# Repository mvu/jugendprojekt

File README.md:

# jugendprojekt
This project has been moved to [gitlab.com](https://gitlab.com/jugendraum-feg-simmern/).

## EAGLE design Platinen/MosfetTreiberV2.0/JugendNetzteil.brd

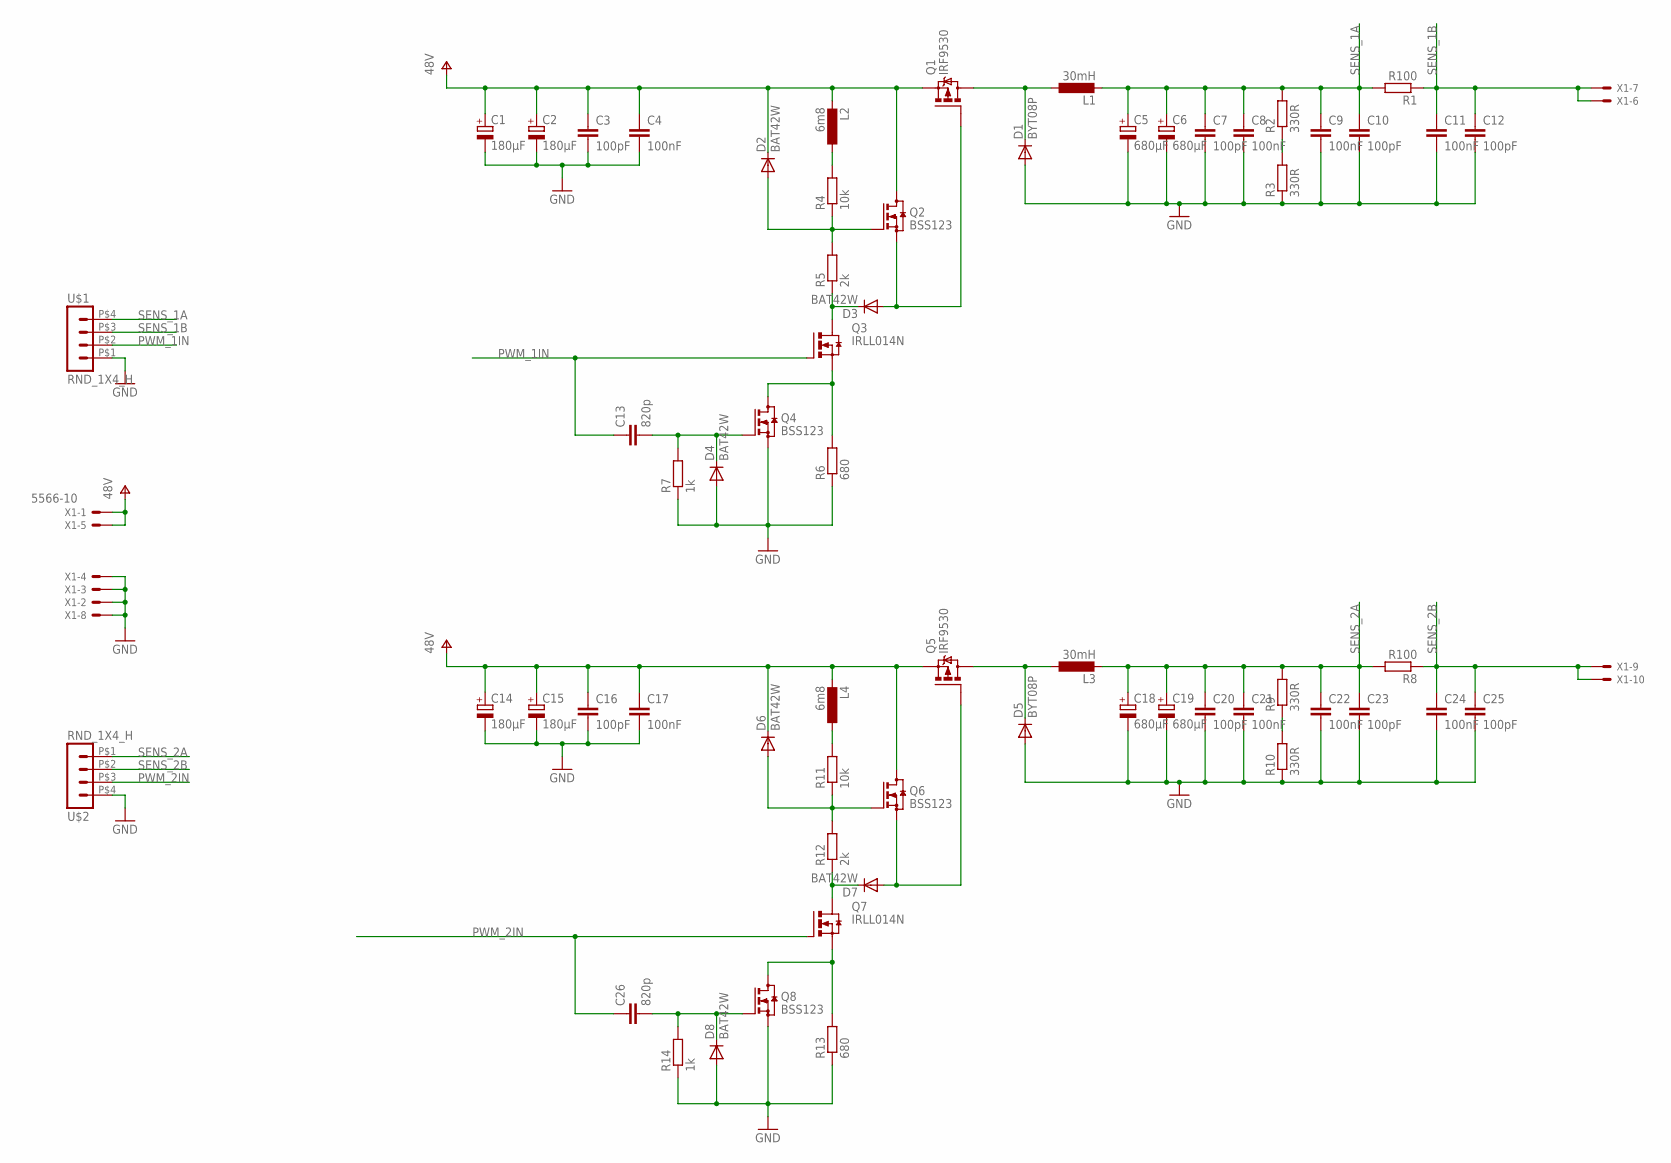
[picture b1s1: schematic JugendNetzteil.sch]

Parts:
C1, C2, C14, C15: 180µF; E3,5-8
C3, C7, C10, C12, C16, C20, C23, C25: 100pF; C0805
C4, C8, C9, C11, C17, C21, C22, C24: 100nF; C0805
C5, C6, C18, C19: 680µF; TT5D11
C13, C26: 820p; C0805
D1, D5: BYT08P; TO220ACS
D2, D3, D4, D6, D7, D8: BAT42W; SOD123
L1, L3: 30mH; TJ8-U1
L2, L4: 6m8; 2200-15.24
Q1, Q5: IRF9530; TO220BV
Q2, Q4, Q6, Q8: BSS123; SOT23
Q3, Q7: IRLL014N; SOT223
R1, R8: R100; 0617V
R2, R3, R9, R10: 330R; 0414V
R4, R11: 10k; R0805
R5, R12: 2k; R0805
R6, R13: 680; R0805
R7, R14: 1k; R0805
U$1, U$2: RND_1X4_H
X1: 5566-10

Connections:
GND: C1.-, C2.-, C3.2, C4.2, C5.-, C6.-, C7.2, C8.2, C9.2, C10.2, C11.2, C12.2, C14.-, C15.-, C16.2, C17.2, C18.-, C19.-, C20.2, C21.2, C22.2, C23.2, C24.2, C25.2, D1.A, D4.A, D5.A, D8.A, Q4.2 (S), Q8.2 (S), R3.1, R6.1, R7.1, R10.1, R13.1, R14.1, U$1.P$1 (1), U$2.P$4 (4), X1.2, X1.3, X1.4, X1.8
unnamed: C13.2, D4.C, Q4.1 (G), R7.2
unnamed: L2.1, R4.2
unnamed: D1.C, L1.1, Q1.D
unnamed: D3.A, Q1.G, Q2.2 (S)
unnamed: D3.C, Q3.2 (D), Q3.4 (D), R5.1
unnamed: D2.A, Q2.1 (G), R4.1, R5.2
unnamed: Q3.3 (S), Q4.3 (D), R6.2
unnamed: D6.A, Q6.1 (G), R11.1, R12.2
unnamed: L4.1, R11.2
unnamed: R2.1, R3.2
unnamed: D7.A, Q5.G, Q6.2 (S)
unnamed: D7.C, Q7.2 (D), Q7.4 (D), R12.1
unnamed: D5.C, L3.1, Q5.D
unnamed: C26.2, D8.C, Q8.1 (G), R14.2
unnamed: Q7.3 (S), Q8.3 (D), R13.2
unnamed: R9.1, R10.2
PWM_1IN: C13.1, Q3.1 (G), U$1.P$2 (2)
PWM_2IN: C26.1, Q7.1 (G), U$2.P$3 (3)
SENS_1A: C5.+, C6.+, C7.1, C8.1, C9.1, C10.1, L1.2, R1.2, R2.2, U$1.P$4 (4)
SENS_1B: C11.1, C12.1, R1.1, U$1.P$3 (3), X1.6, X1.7
SENS_2A: C18.+, C19.+, C20.1, C21.1, C22.1, C23.1, L3.2, R8.2, R9.2, U$2.P$1 (1)
SENS_2B: C24.1, C25.1, R8.1, U$2.P$2 (2), X1.9, X1.10
V+: C1.+, C2.+, C3.1, C4.1, C14.+, C15.+, C16.1, C17.1, D2.C, D6.C, L2.2, L4.2, Q1.S, Q2.3 (D), Q5.S, Q6.3 (D), X1.1, X1.5

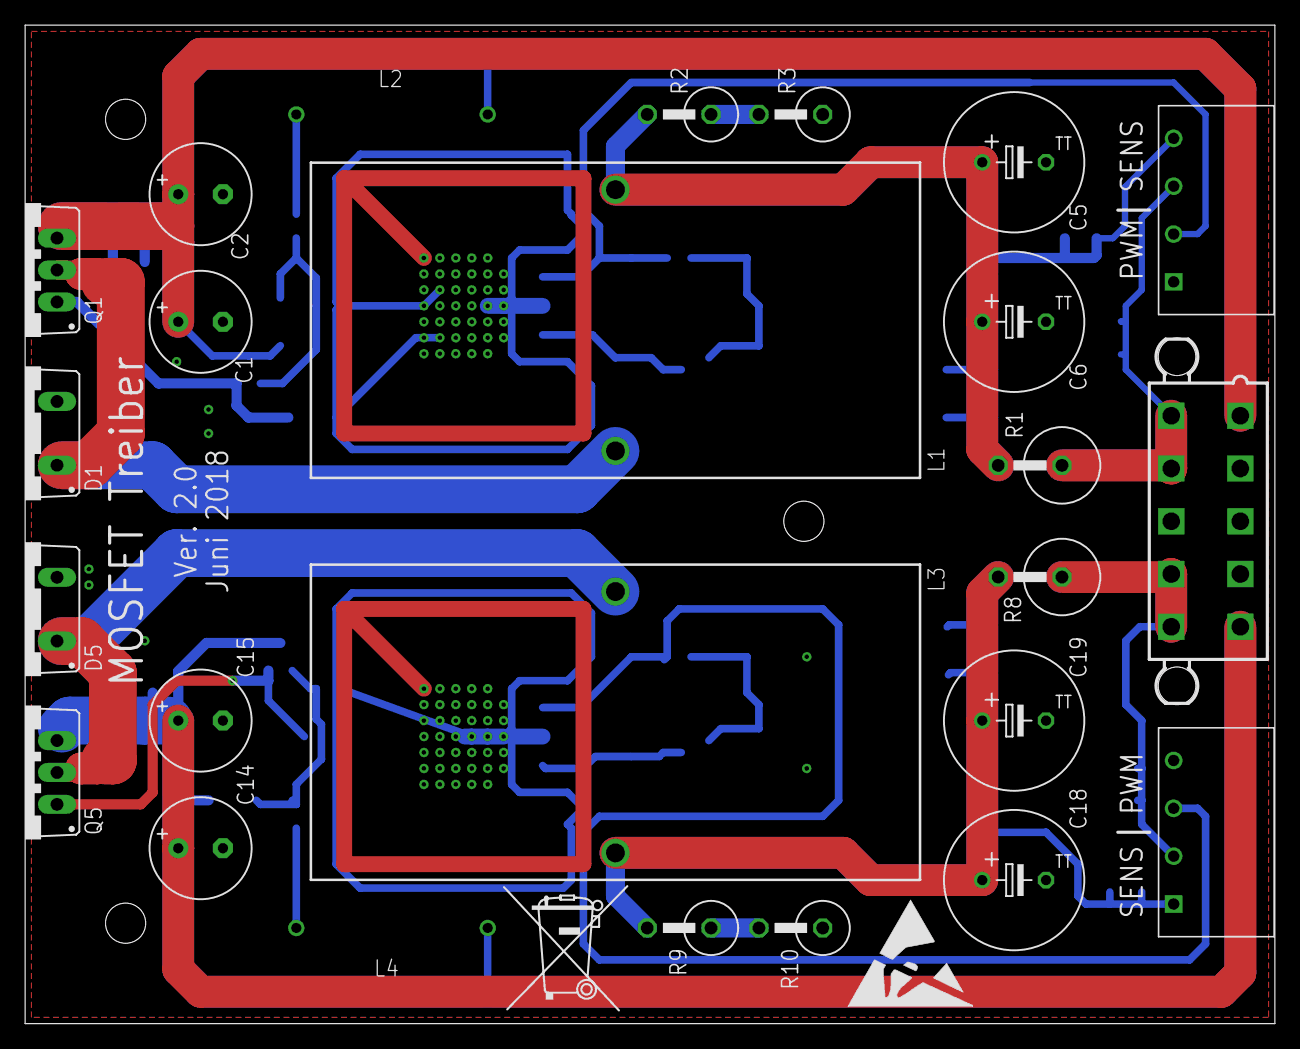
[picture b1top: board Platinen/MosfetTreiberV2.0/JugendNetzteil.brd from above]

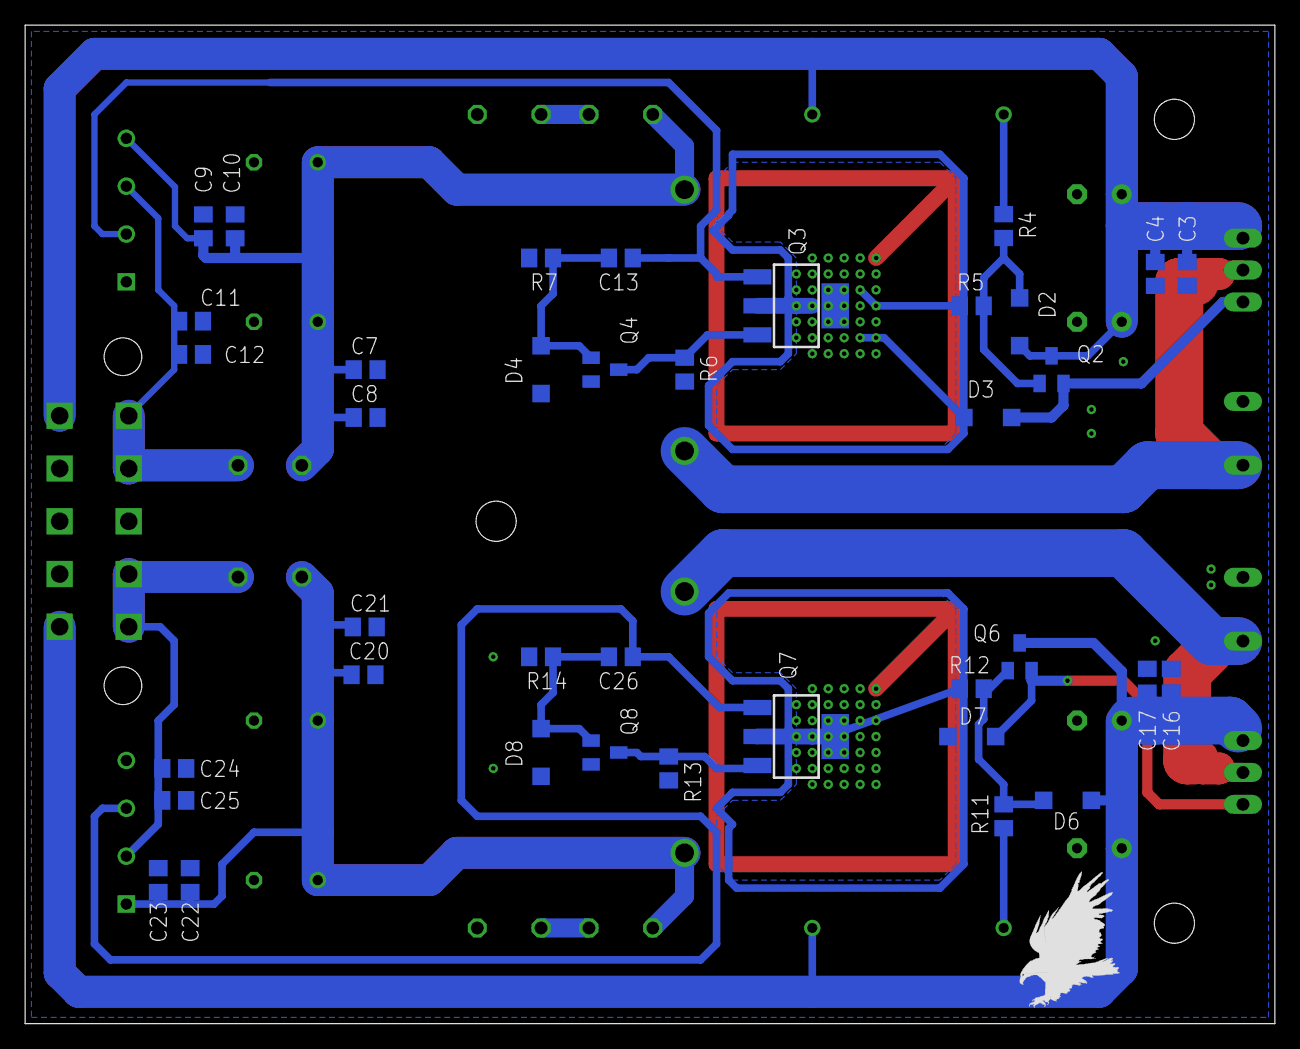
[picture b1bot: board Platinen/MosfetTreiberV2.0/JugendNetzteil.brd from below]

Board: 2 copper layers, 99.5 x 79.5 mm, 66 parts (39 on the bottom side), 24 nets.

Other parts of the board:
U$3: EAGLE-PLC-8MM
U$4: ESD_10.00
U$5: MUELLTONNE_10.00

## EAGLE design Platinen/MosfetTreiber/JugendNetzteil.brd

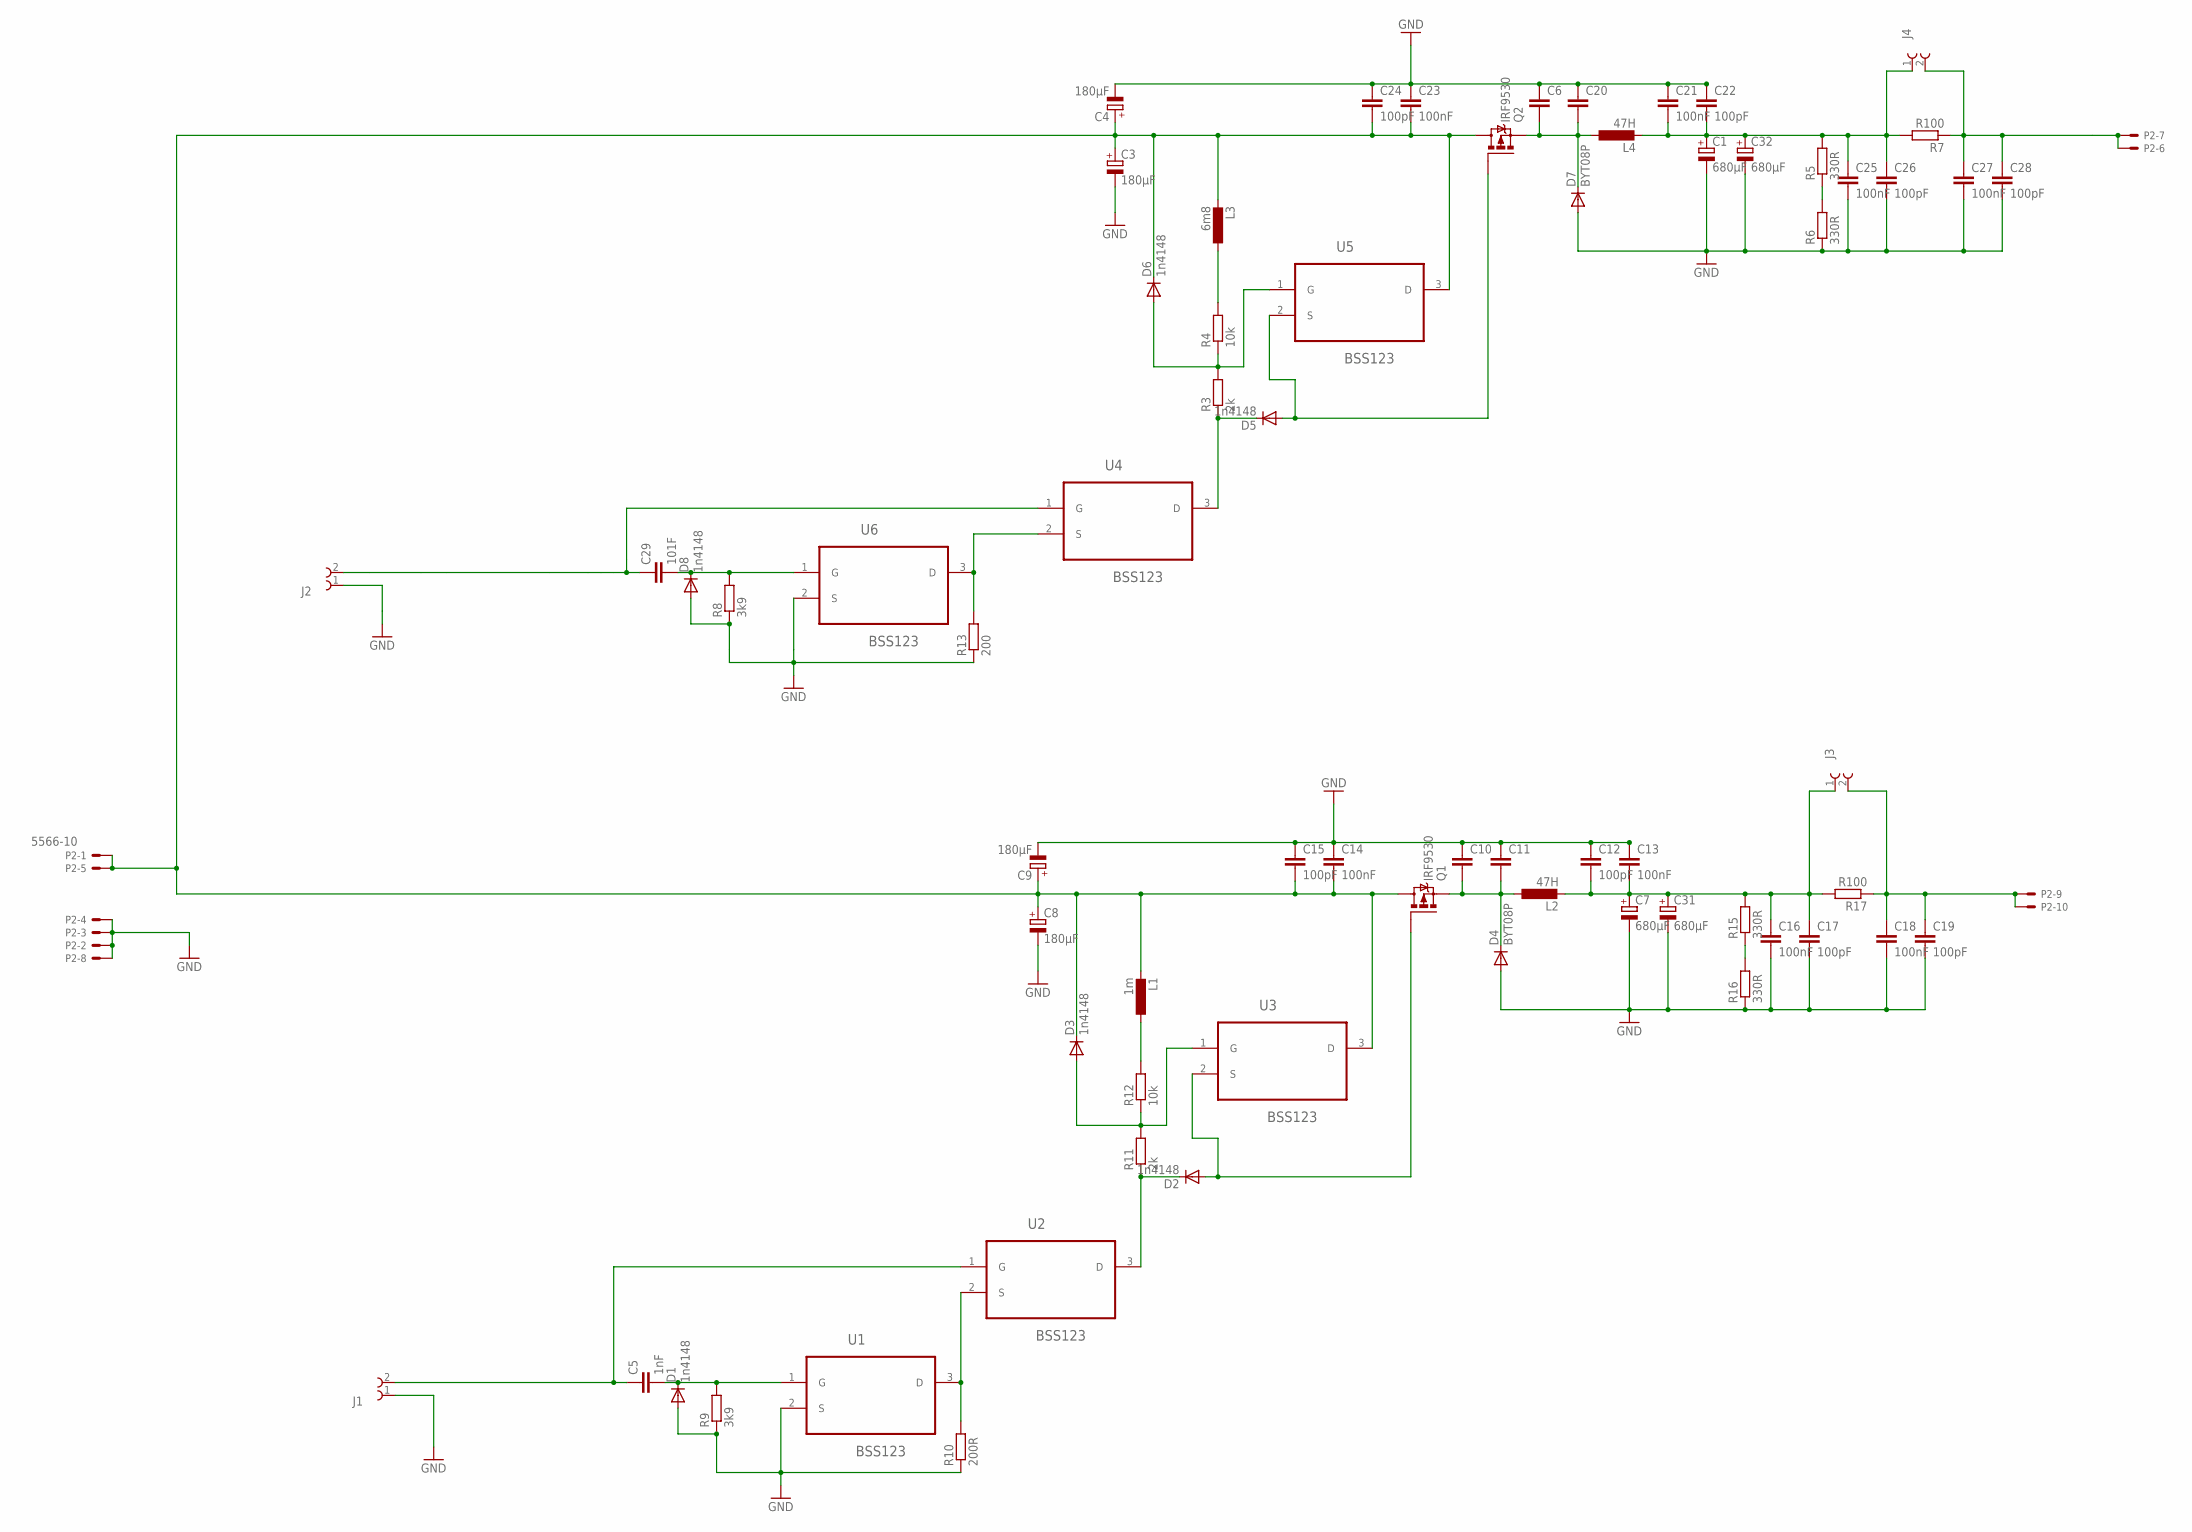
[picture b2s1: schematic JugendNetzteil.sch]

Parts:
C1, C7, C31, C32: 680µF; TT5D11
C3, C4, C8, C9: 180µF; E5-8,5
C5: 1nF; C0805
C6, C10, C11, C20: C-EUC1206; C1206
C12, C15, C17, C19, C22, C24, C26, C28: 100pF; C1206
C13, C14, C16, C18, C21, C23, C25, C27: 100nF; C1206
C29: 101F; C0805
D1, D2, D3, D5, D6, D8: 1n4148; MINIMELF
D4, D7: BYT08P; TO220ACS
J1, J2, J3, J4: 691210910002
L1: 1m; 0207/15
L2, L4: 47H; TJ8-U1
L3: 6m8; 0207/15
P2: 5566-10
Q1, Q2: IRF9530; TO220BV
R3, R11: 2k; R0805
R4, R12: 10k; R0805
R5, R6, R15, R16: 330R; P0817V
R7, R17: R100; P0817V
R8, R9: 3k9; R0805
R10: 200R; R0805
R13: 200; R0805
U1, U2, U3, U4, U5, U6: BSS123; SOT95P280X130-3N

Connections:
+48V: C3.+, C4.+, C8.+, C9.+, C14.2, C15.2, C23.2, C24.2, D3.C, D6.C, L1.2, L3.2, P2.1, P2.5, Q1.D, Q2.D, U3.3 (D), U5.3 (D)
GND: C1.-, C3.-, C4.-, C6.1, C7.-, C8.-, C9.-, C10.1, C11.1, C12.1, C13.1, C14.1, C15.1, C16.2, C17.2, C18.2, C19.2, C20.1, C21.1, C22.1, C23.1, C24.1, C25.2, C26.2, C27.2, C28.2, C31.-, C32.-, D1.A, D4.A, D7.A, D8.A, J1.1, J2.1, P2.2, P2.3, P2.4, P2.8, R6.1, R8.1, R9.1, R10.1, R13.1, R16.1, U1.2 (S), U6.2 (S)
unnamed: C5.1, J1.2, U2.1 (G)
unnamed: C29.1, J2.2, U4.1 (G)
unnamed: D6.A, R3.2, R4.1, U5.1 (G)
unnamed: D5.A, Q2.G, U5.2 (S)
unnamed: D3.A, R11.2, R12.1, U3.1 (G)
unnamed: D5.C, R3.1, U4.3 (D)
unnamed: D2.A, Q1.G, U3.2 (S)
unnamed: L3.1, R4.2
unnamed: D2.C, R11.1, U2.3 (D)
unnamed: R10.2, U1.3 (D), U2.2 (S)
unnamed: C6.2, C20.2, D7.C, L4.1, Q2.S
unnamed: C1.+, C21.2, C22.2, C25.1, C26.1, C32.+, J4.1, L4.2, R5.2, R7.2
unnamed: R5.1, R6.2
unnamed: C5.2, D1.C, R9.2, U1.1 (G)
unnamed: L1.1, R12.2
unnamed: C10.2, C11.2, D4.C, L2.1, Q1.S
unnamed: C7.+, C12.2, C13.2, C16.1, C17.1, C31.+, J3.1, L2.2, R15.2, R17.2
unnamed: R13.2, U4.2 (S), U6.3 (D)
unnamed: R15.1, R16.2
unnamed: C29.2, D8.C, R8.2, U6.1 (G)
OUT1: C18.1, C19.1, J3.2, P2.9, P2.10, R17.1
OUT2: C27.1, C28.1, J4.2, P2.6, P2.7, R7.1

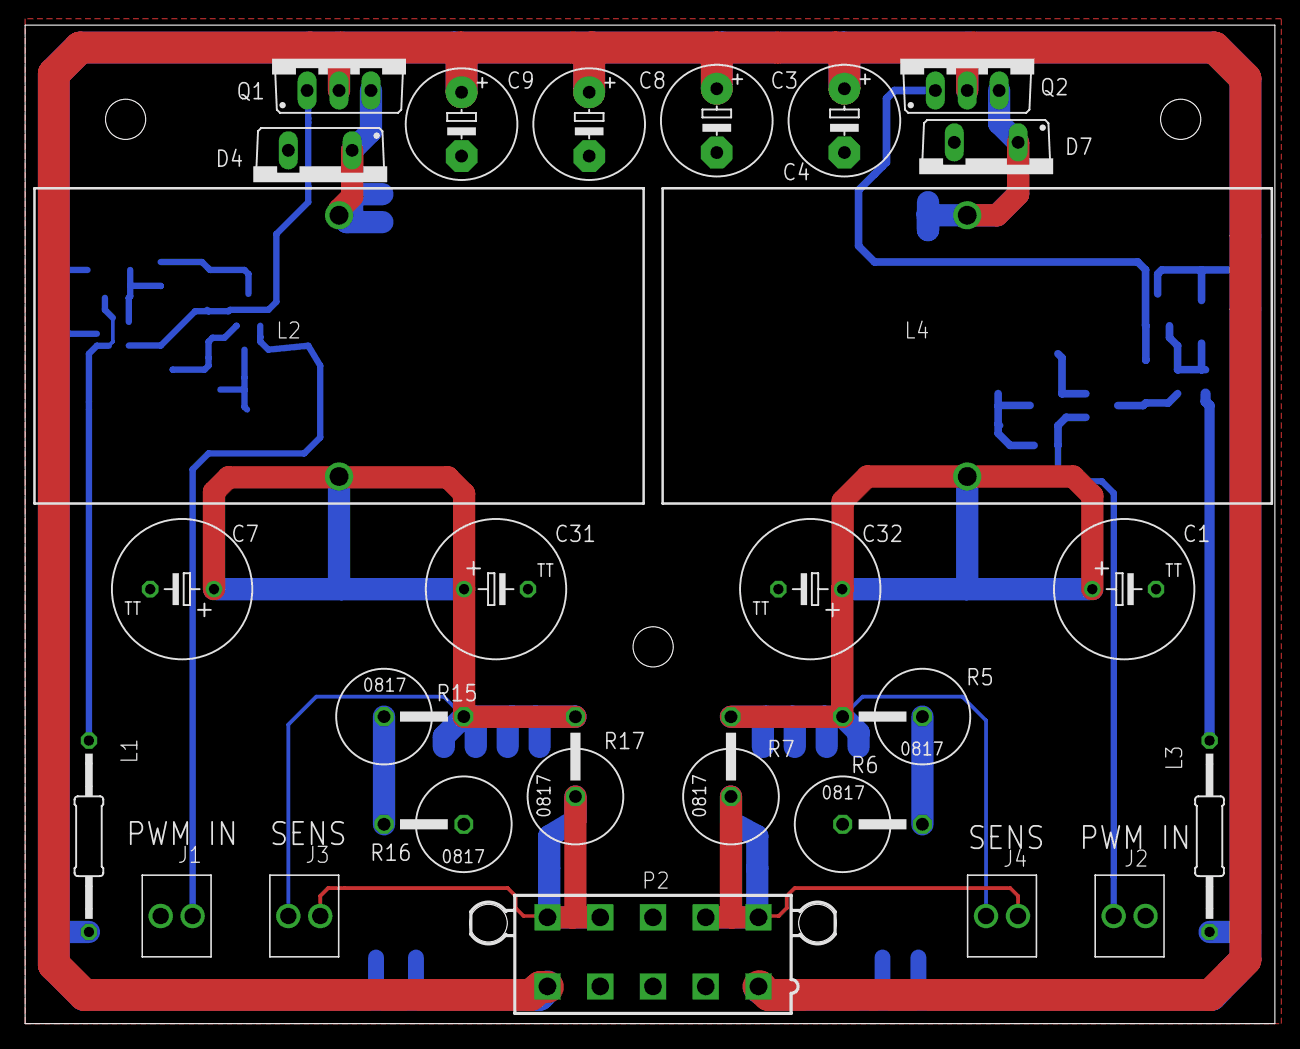
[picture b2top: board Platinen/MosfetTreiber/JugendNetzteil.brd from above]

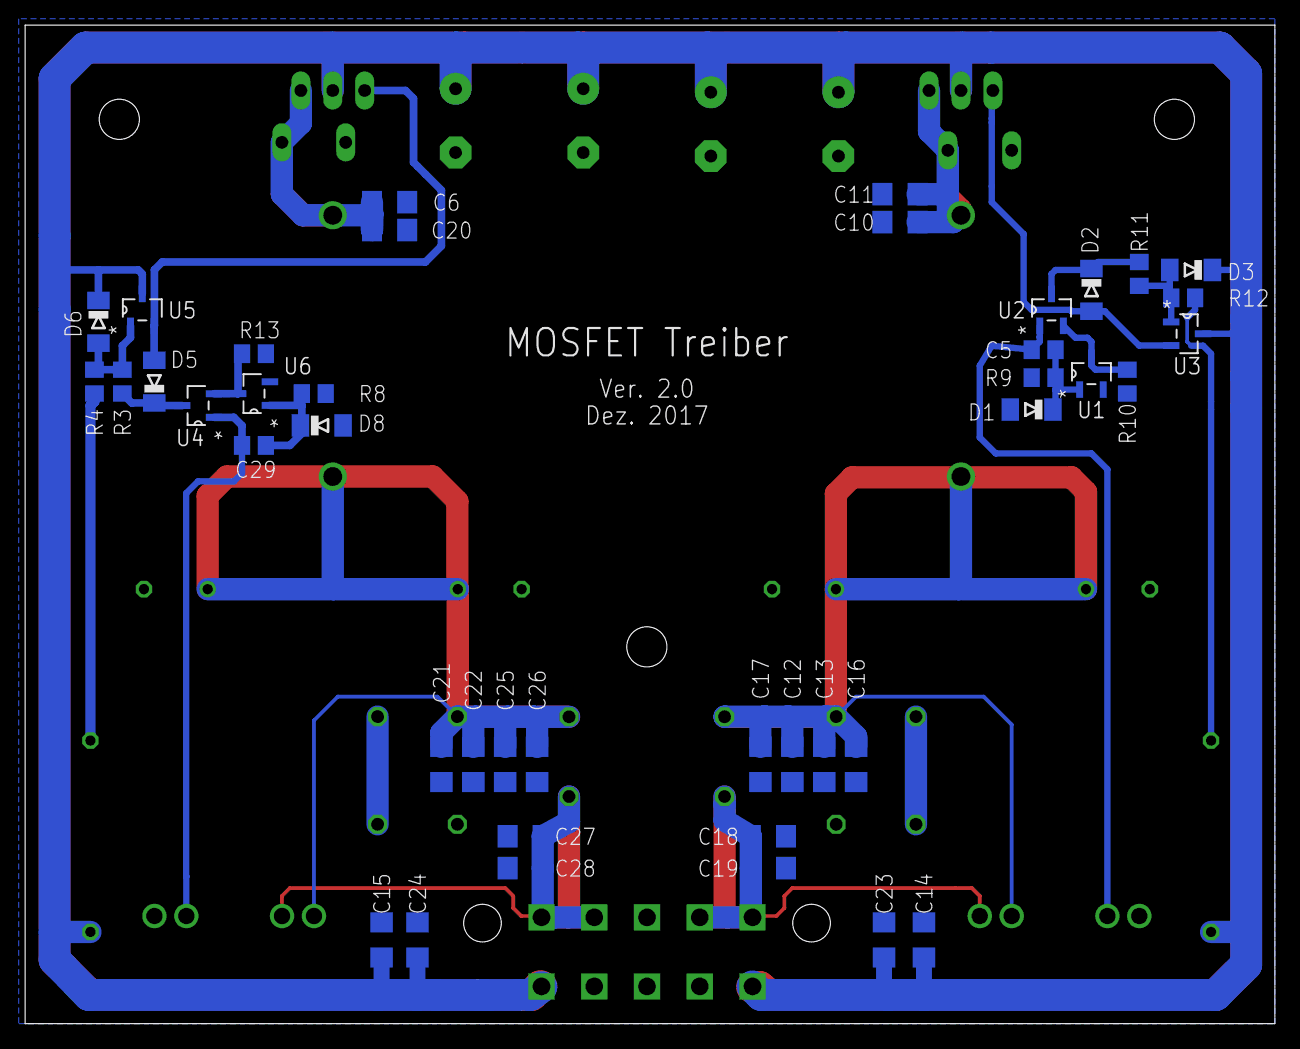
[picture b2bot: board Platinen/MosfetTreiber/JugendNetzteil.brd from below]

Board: 2 copper layers, 99.5 x 79.5 mm, 69 parts (42 on the bottom side), 24 nets.

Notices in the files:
parts and their libraries:
WR-TBL: Copyright: Würth Elektronik
Volks73-NXPSemiconductors: Creative Commons Attribution-ShareAlike 3.0 Unported (CC BY-SA 3.0), http://creativecommons.org/licenses/by-sa/3.0/.
